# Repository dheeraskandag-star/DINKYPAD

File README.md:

# DINKYPAD
It is a 3-key macropad which i plan on using for music control.It consists of an oled display for cool animations, an rotary encoder for volume control and rgb leds for lighting.

I would be using the keys for media control and rotay encoder for volume control.

It would be so much easier with this micropad to control music and media playback.

CAD:

PCB:

Schematic:

BOM:
-3x cherry mx switches,
-3x blank DSA switches,
-3x SK6812 MINI-E LED,
-1x 0.91" 128x32 OLED Display,
-1x EC11rotary encoder,
-1x XIAO RP2040,

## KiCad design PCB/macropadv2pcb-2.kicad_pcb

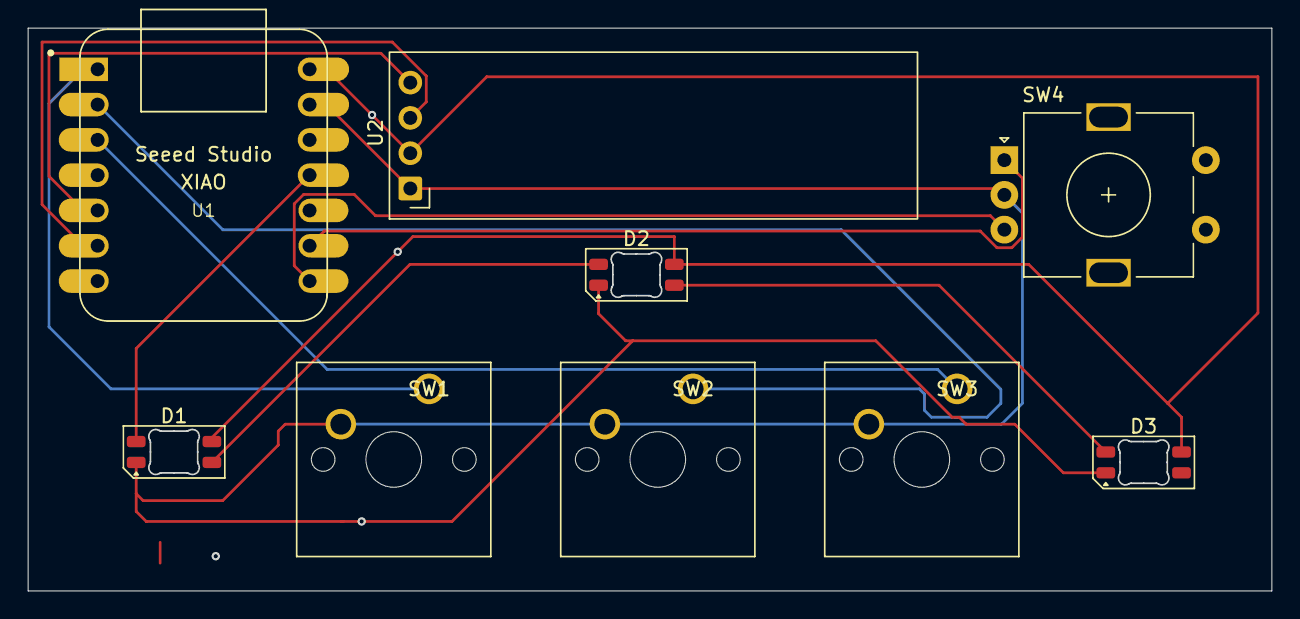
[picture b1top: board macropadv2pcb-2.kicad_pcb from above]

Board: 2 copper layers, 89.4 x 40.4 mm, 9 parts (0 on the bottom side), 12 nets.

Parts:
D1, D2, D3: SK6812MINI-E; LED_SK6812MINI-E_3.2x2.8mm_P1.5mm_ReverseMount
SW1, SW2, SW3: SW_Push; SW_Cherry_MX_1.00u_PCB
SW4: RotaryEncoder_Switch; RotaryEncoder_Alps_EC11E-Switch_Vertical_H20mm
U1: MOUDLE-SEEEDUINO-XIAO; XIAO-Generic-Hybrid-14P-2.54-21X17.8MM
U2: ER_OLEDM0.91_1x-I2C

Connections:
GND: D1.1 (VSS), D2.1 (VSS), D3.1 (VSS), SW1.2, SW2.2, SW3.2, SW4.C, U1.13 (GND), U2.1 (GND)
unnamed: D1.2 (DIN), U1.11 (PA6_A10_D10_MOSI)
unnamed: D1.4 (DOUT), D2.2 (DIN)
unnamed: D2.4 (DOUT), D3.2 (DIN)
unnamed: SW1.1, U1.1 (PA02_A0_D0)
unnamed: SW2.1, U1.2 (PA4_A1_D1)
unnamed: SW4.A, U1.9 (PA7_A8_D8_SCK)
unnamed: U1.5 (PA8_A4_D4_SDA), U2.4 (SDA)
unnamed: U1.6 (PA9_A5_D5_SCL), U2.3 (SCL)
unnamed: SW3.1, U1.3 (PA10_A2_D2)
unnamed: SW4.B, U1.8 (PB09_A7_D7_RX)
VCC: D1.3 (VDD), D2.3 (VDD), D3.3 (VDD), U1.14 (5V), U2.2 (VCC)

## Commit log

2026-03-29 Enhance README with project details and images
    Added images and improved description for the DINKYPAD project.
2026-03-29 Create firmware
2026-03-29 Add firmware code for HID and LED control
2026-03-30 Update readme with hardware and setup details
    Added hardware and setup instructions for the project.
2026-03-30 Add additional image to README.md
2026-03-30 Create gerbers
2026-03-30 Rename 12345.zip to gerber.zip
2026-03-30 Create s
2026-03-30 Rename PCB/12345.zip to gerber.zip
2026-03-30 Create u
2026-03-30 Create bk
2026-03-30 Rename PCB/untitled.kicad_sch to macropad.kicad_sch
2026-03-30 Create
2026-03-30 Create k
